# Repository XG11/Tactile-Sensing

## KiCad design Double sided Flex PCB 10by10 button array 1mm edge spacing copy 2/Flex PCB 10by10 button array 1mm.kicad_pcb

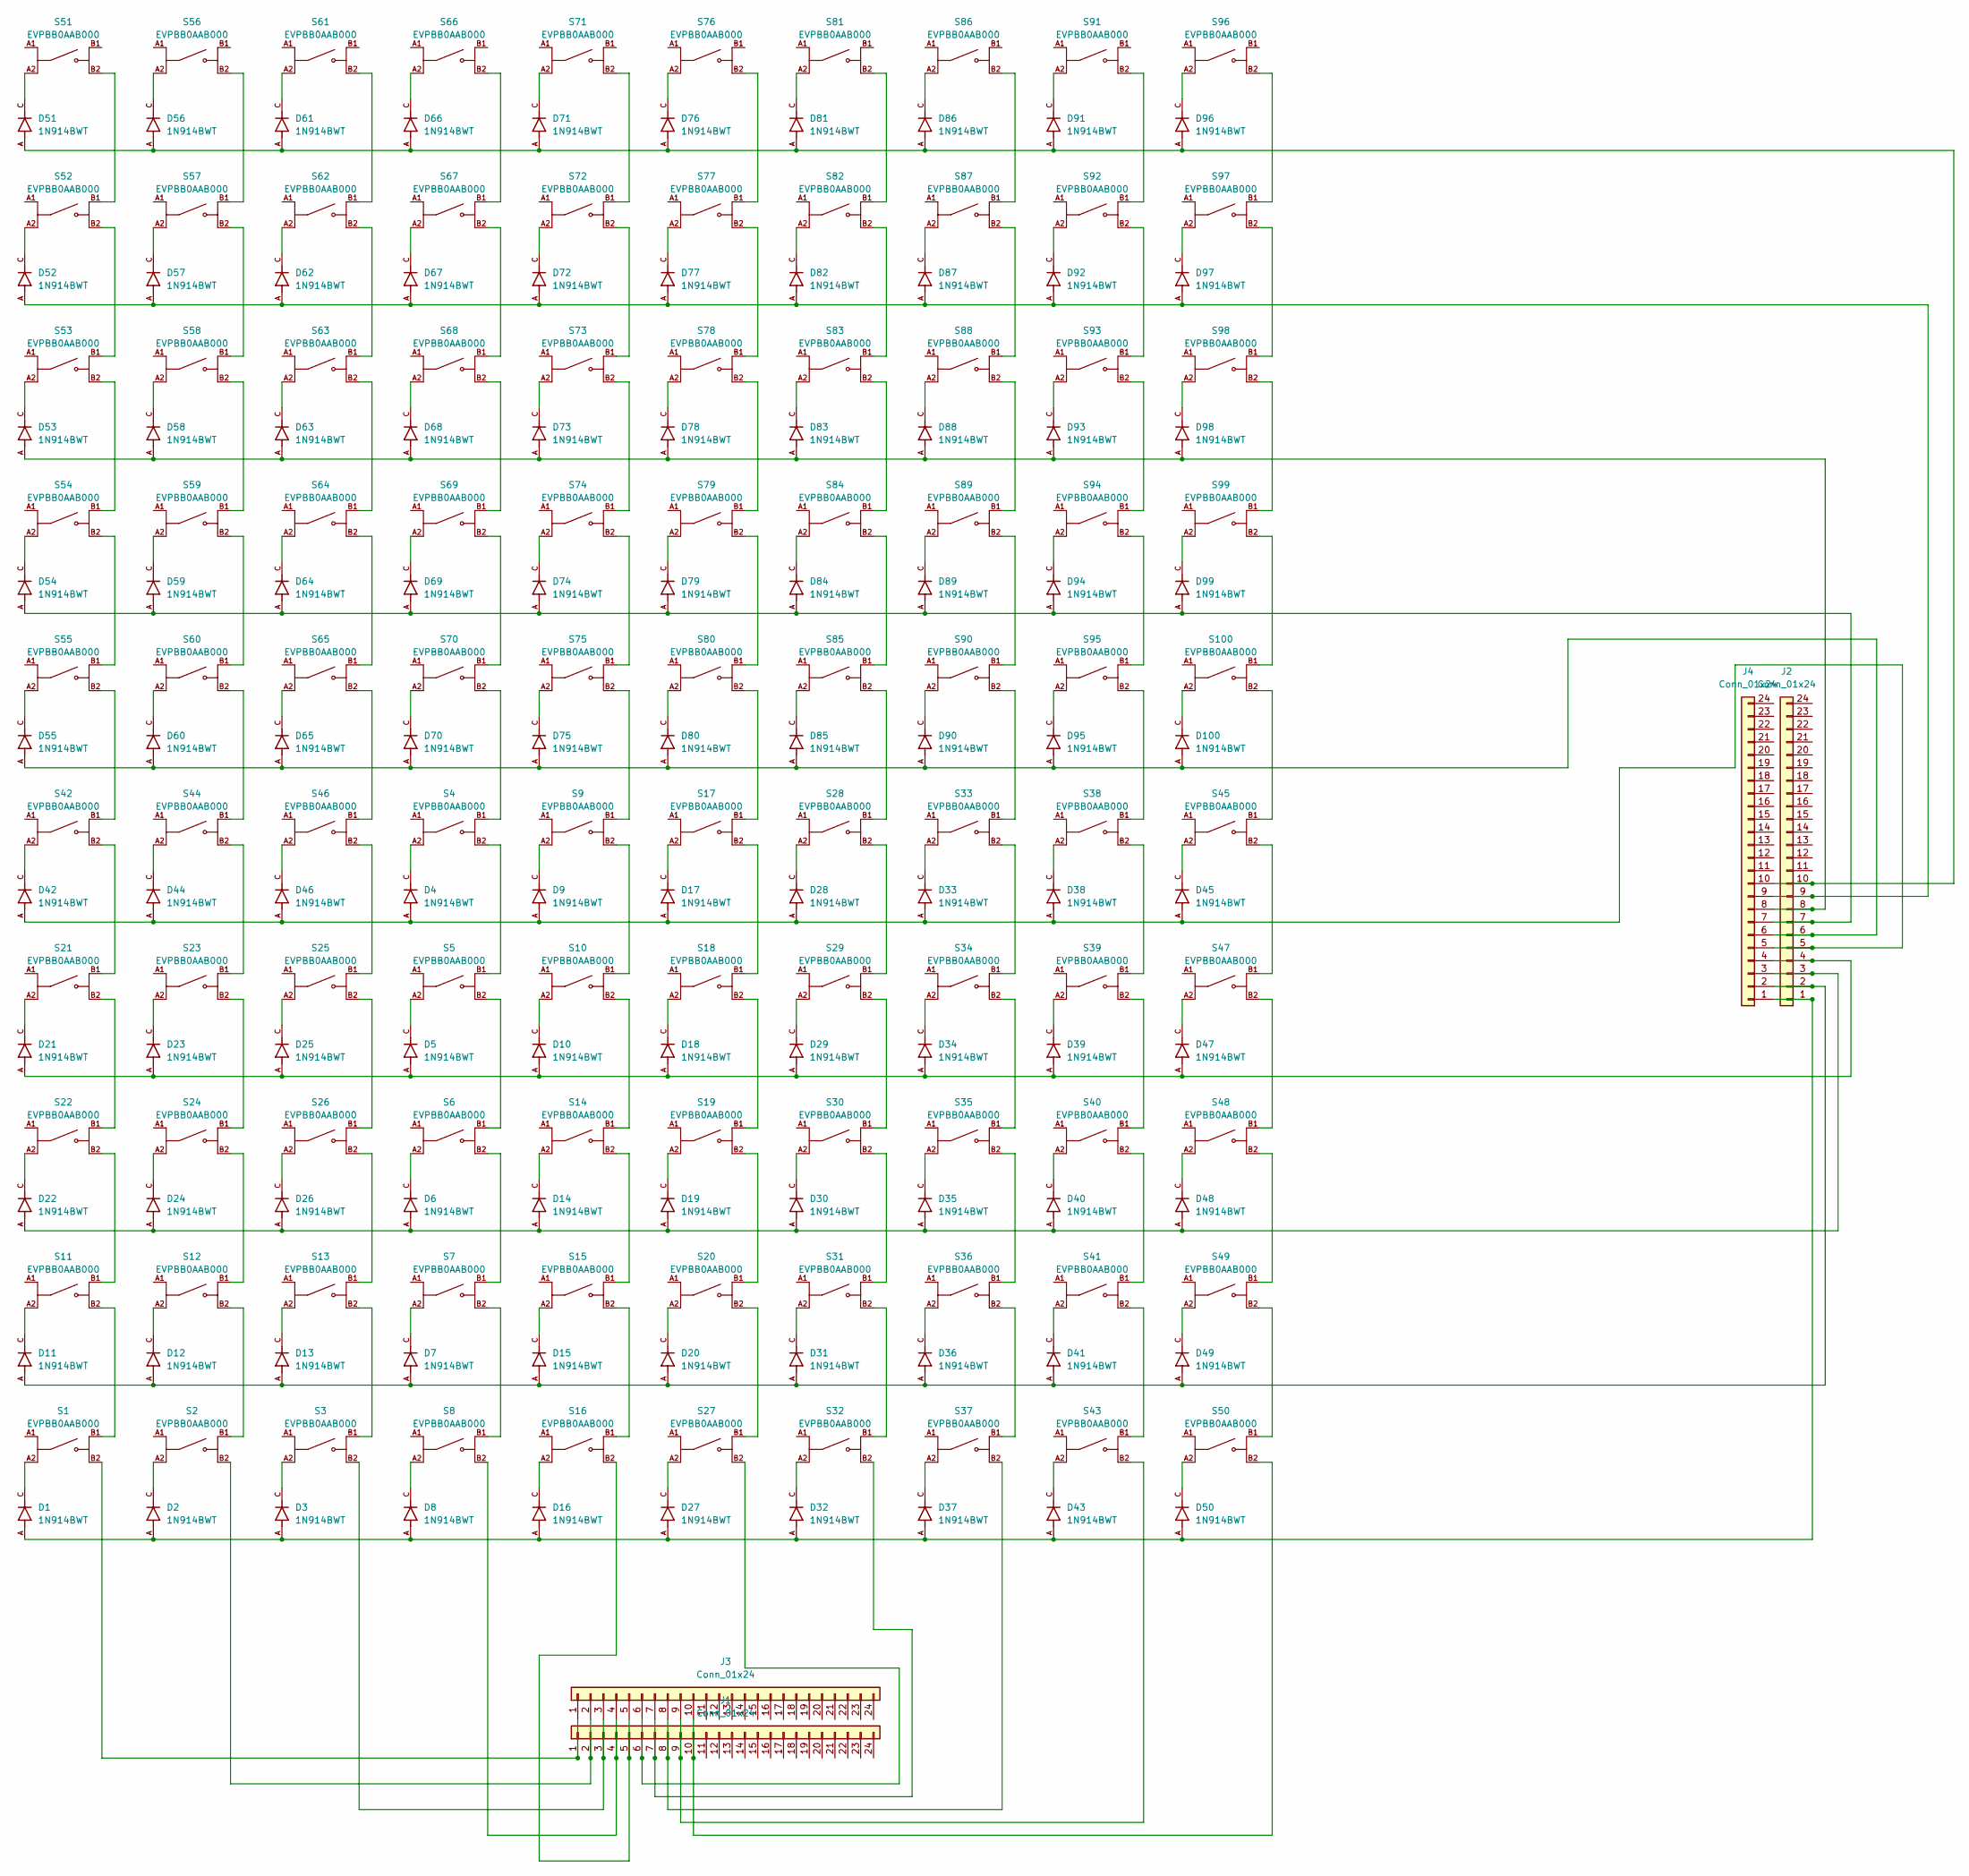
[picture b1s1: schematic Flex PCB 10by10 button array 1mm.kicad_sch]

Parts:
D1, D2, D3, D4, D5, D6, D7, D8, D9, D10, D11, D12, D13, D14, D15, D16, D17, D18, D19, D20, D21, D22, D23, D24, D25, D26, D27, D28, D29, D30, D31, D32, D33, D34, D35, D36, D37, D38, D39, D40, D41, D42, D43, D44, D45, D46, D47, D48, D49, D50, D51, D52, D53, D54, D55, D56, D57, D58, D59, D60, D61, D62, D63, D64, D65, D66, D67, D68, D69, D70, D71, D72, D73, D74, D75, D76, D77, D78, D79, D80, D81, D82, D83, D84, D85, D86, D87, D88, D89, D90, D91, D92, D93, D94, D95, D96, D97, D98, D99, D100: 1N914BWT; SODFL1608X70N; PARTREV A2
J1, J2, J3, J4: Conn_01x24; 24pos edge connector
S1, S2, S3, S4, S5, S6, S7, S8, S9, S10, S11, S12, S13, S14, S15, S16, S17, S18, S19, S20, S21, S22, S23, S24, S25, S26, S27, S28, S29, S30, S31, S32, S33, S34, S35, S36, S37, S38, S39, S40, S41, S42, S43, S44, S45, S46, S47, S48, S49, S50, S51, S52, S53, S54, S55, S56, S57, S58, S59, S60, S61, S62, S63, S64, S65, S66, S67, S68, S69, S70, S71, S72, S73, S74, S75, S76, S77, S78, S79, S80, S81, S82, S83, S84, S85, S86, S87, S88, S89, S90, S91, S92, S93, S94, S95, S96, S97, S98, S99, S100: EVPBB0AAB000; SW_EVPBB0AAB000; DIGI-KEY_PART_NUMBER P19888CT-ND

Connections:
unnamed: D1.C, S1.A2
unnamed: D2.C, S2.A2
unnamed: D3.C, S3.A2
unnamed: D4.C, S4.A2
unnamed: D5.C, S5.A2
unnamed: D6.C, S6.A2
unnamed: D7.C, S7.A2
unnamed: D8.C, S8.A2
unnamed: D9.C, S9.A2
unnamed: D10.C, S10.A2
unnamed: D11.C, S11.A2
unnamed: D12.C, S12.A2
unnamed: D13.C, S13.A2
unnamed: D14.C, S14.A2
unnamed: D15.C, S15.A2
unnamed: D16.C, S16.A2
unnamed: D17.C, S17.A2
unnamed: D18.C, S18.A2
unnamed: D19.C, S19.A2
unnamed: D20.C, S20.A2
unnamed: D21.C, S21.A2
unnamed: D22.C, S22.A2
unnamed: D23.C, S23.A2
unnamed: D24.C, S24.A2
unnamed: D25.C, S25.A2
unnamed: D26.C, S26.A2
unnamed: D27.C, S27.A2
unnamed: D28.C, S28.A2
unnamed: D29.C, S29.A2
unnamed: D30.C, S30.A2
unnamed: D31.C, S31.A2
unnamed: D32.C, S32.A2
unnamed: D33.C, S33.A2
unnamed: D34.C, S34.A2
unnamed: D35.C, S35.A2
unnamed: D36.C, S36.A2
unnamed: D37.C, S37.A2
unnamed: D38.C, S38.A2
unnamed: D39.C, S39.A2
unnamed: D40.C, S40.A2
unnamed: D41.C, S41.A2
unnamed: D42.C, S42.A2
unnamed: D43.C, S43.A2
unnamed: D44.C, S44.A2
unnamed: D45.C, S45.A2
unnamed: D46.C, S46.A2
unnamed: D47.C, S47.A2
unnamed: D48.C, S48.A2
unnamed: D49.C, S49.A2
unnamed: D50.C, S50.A2
unnamed: D51.C, S51.A2
unnamed: D52.C, S52.A2
unnamed: D53.C, S53.A2
unnamed: D54.C, S54.A2
unnamed: D55.C, S55.A2
unnamed: D56.C, S56.A2
unnamed: D57.C, S57.A2
unnamed: D58.C, S58.A2
unnamed: D59.C, S59.A2
unnamed: D60.C, S60.A2
unnamed: D61.C, S61.A2
unnamed: D62.C, S62.A2
unnamed: D63.C, S63.A2
unnamed: D64.C, S64.A2
unnamed: D65.C, S65.A2
unnamed: D66.C, S66.A2
unnamed: D67.C, S67.A2
unnamed: D68.C, S68.A2
unnamed: D69.C, S69.A2
unnamed: D70.C, S70.A2
unnamed: D71.C, S71.A2
unnamed: D72.C, S72.A2
unnamed: D73.C, S73.A2
unnamed: D74.C, S74.A2
unnamed: D75.C, S75.A2
unnamed: D76.C, S76.A2
unnamed: D77.C, S77.A2
unnamed: D78.C, S78.A2
unnamed: D79.C, S79.A2
unnamed: D80.C, S80.A2
unnamed: D81.C, S81.A2
unnamed: D82.C, S82.A2
unnamed: D83.C, S83.A2
unnamed: D84.C, S84.A2
unnamed: D85.C, S85.A2
unnamed: D86.C, S86.A2
unnamed: D87.C, S87.A2
unnamed: D88.C, S88.A2
unnamed: D89.C, S89.A2
unnamed: D90.C, S90.A2
unnamed: D91.C, S91.A2
unnamed: D92.C, S92.A2
unnamed: D93.C, S93.A2
unnamed: D94.C, S94.A2
unnamed: D95.C, S95.A2
unnamed: D96.C, S96.A2
unnamed: D97.C, S97.A2
unnamed: D98.C, S98.A2
unnamed: D99.C, S99.A2
unnamed: D100.C, S100.A2
unnamed: J1.1, J3.1, S1.B2
unnamed: J1.2, J3.2, S2.B2
unnamed: J1.3, J3.3, S3.B2
unnamed: J1.4, J3.4, S8.B2
unnamed: J1.5, J3.5, S16.B2
unnamed: J1.6, J3.6, S27.B2
unnamed: J1.7, J3.7, S32.B2
unnamed: J1.8, J3.8, S37.B2
unnamed: J1.9, J3.9, S43.B2
unnamed: J1.10, J3.10, S50.B2
unnamed: D1.A, D2.A, D3.A, D8.A, D16.A, D27.A, D32.A, D37.A, D43.A, D50.A, J2.1, J4.1
unnamed: D7.A, D11.A, D12.A, D13.A, D15.A, D20.A, D31.A, D36.A, D41.A, D49.A, J2.2, J4.2
unnamed: D6.A, D14.A, D19.A, D22.A, D24.A, D26.A, D30.A, D35.A, D40.A, D48.A, J2.3, J4.3
unnamed: D5.A, D10.A, D18.A, D21.A, D23.A, D25.A, D29.A, D34.A, D39.A, D47.A, J2.4, J4.4
unnamed: D4.A, D9.A, D17.A, D28.A, D33.A, D38.A, D42.A, D44.A, D45.A, D46.A, J2.5, J4.5
unnamed: D55.A, D60.A, D65.A, D70.A, D75.A, D80.A, D85.A, D90.A, D95.A, D100.A, J2.6, J4.6
unnamed: D54.A, D59.A, D64.A, D69.A, D74.A, D79.A, D84.A, D89.A, D94.A, D99.A, J2.7, J4.7
unnamed: D53.A, D58.A, D63.A, D68.A, D73.A, D78.A, D83.A, D88.A, D93.A, D98.A, J2.8, J4.8
unnamed: D52.A, D57.A, D62.A, D67.A, D72.A, D77.A, D82.A, D87.A, D92.A, D97.A, J2.9, J4.9
unnamed: D51.A, D56.A, D61.A, D66.A, D71.A, D76.A, D81.A, D86.A, D91.A, D96.A, J2.10, J4.10
unnamed: S1.B1, S11.B2
unnamed: S4.B1, S70.B2
unnamed: S4.B2, S5.B1
unnamed: S5.B2, S6.B1
unnamed: S6.B2, S7.B1
unnamed: S7.B2, S8.B1
unnamed: S9.B2, S10.B1
unnamed: S10.B2, S14.B1
unnamed: S11.B1, S22.B2
unnamed: S12.B1, S24.B2
unnamed: S2.B1, S12.B2
unnamed: S13.B1, S26.B2
unnamed: S3.B1, S13.B2
unnamed: S14.B2, S15.B1
unnamed: S15.B2, S16.B1
unnamed: S17.B1, S80.B2
unnamed: S17.B2, S18.B1
unnamed: S18.B2, S19.B1
unnamed: S19.B2, S20.B1
unnamed: S20.B2, S27.B1
unnamed: S21.B1, S42.B2
unnamed: S21.B2, S22.B1
unnamed: S23.B1, S44.B2
unnamed: S23.B2, S24.B1
unnamed: S25.B1, S46.B2
unnamed: S25.B2, S26.B1
unnamed: S28.B1, S85.B2
unnamed: S28.B2, S29.B1
unnamed: S29.B2, S30.B1
unnamed: S30.B2, S31.B1
unnamed: S31.B2, S32.B1
unnamed: S33.B1, S90.B2
unnamed: S33.B2, S34.B1
unnamed: S34.B2, S35.B1
unnamed: S35.B2, S36.B1
unnamed: S36.B2, S37.B1
unnamed: S38.B1, S95.B2
unnamed: S38.B2, S39.B1
unnamed: S39.B2, S40.B1
unnamed: S40.B2, S41.B1
unnamed: S41.B2, S43.B1
unnamed: S42.B1, S55.B2
unnamed: S44.B1, S60.B2
unnamed: S45.B2, S47.B1
unnamed: S46.B1, S65.B2
unnamed: S47.B2, S48.B1
unnamed: S48.B2, S49.B1
unnamed: S49.B2, S50.B1
unnamed: S51.B2, S52.B1
unnamed: S52.B2, S53.B1
unnamed: S53.B2, S54.B1
unnamed: S54.B2, S55.B1
unnamed: S56.B2, S57.B1
unnamed: S57.B2, S58.B1
unnamed: S58.B2, S59.B1
unnamed: S59.B2, S60.B1
unnamed: S61.B2, S62.B1
unnamed: S62.B2, S63.B1
unnamed: S63.B2, S64.B1
unnamed: S64.B2, S65.B1
unnamed: S66.B2, S67.B1
unnamed: S67.B2, S68.B1
unnamed: S68.B2, S69.B1
unnamed: S69.B2, S70.B1
unnamed: S71.B2, S72.B1
unnamed: S72.B2, S73.B1
unnamed: S73.B2, S74.B1
unnamed: S74.B2, S75.B1
unnamed: S9.B1, S75.B2
unnamed: S76.B2, S77.B1
unnamed: S77.B2, S78.B1
unnamed: S78.B2, S79.B1
unnamed: S79.B2, S80.B1
unnamed: S81.B2, S82.B1
unnamed: S82.B2, S83.B1
unnamed: S83.B2, S84.B1
unnamed: S84.B2, S85.B1
unnamed: S86.B2, S87.B1
unnamed: S87.B2, S88.B1
unnamed: S88.B2, S89.B1
unnamed: S89.B2, S90.B1
unnamed: S91.B2, S92.B1
unnamed: S92.B2, S93.B1
unnamed: S93.B2, S94.B1
unnamed: S94.B2, S95.B1
unnamed: S96.B2, S97.B1
unnamed: S97.B2, S98.B1
unnamed: S98.B2, S99.B1
unnamed: S99.B2, S100.B1
unnamed: S45.B1, S100.B2

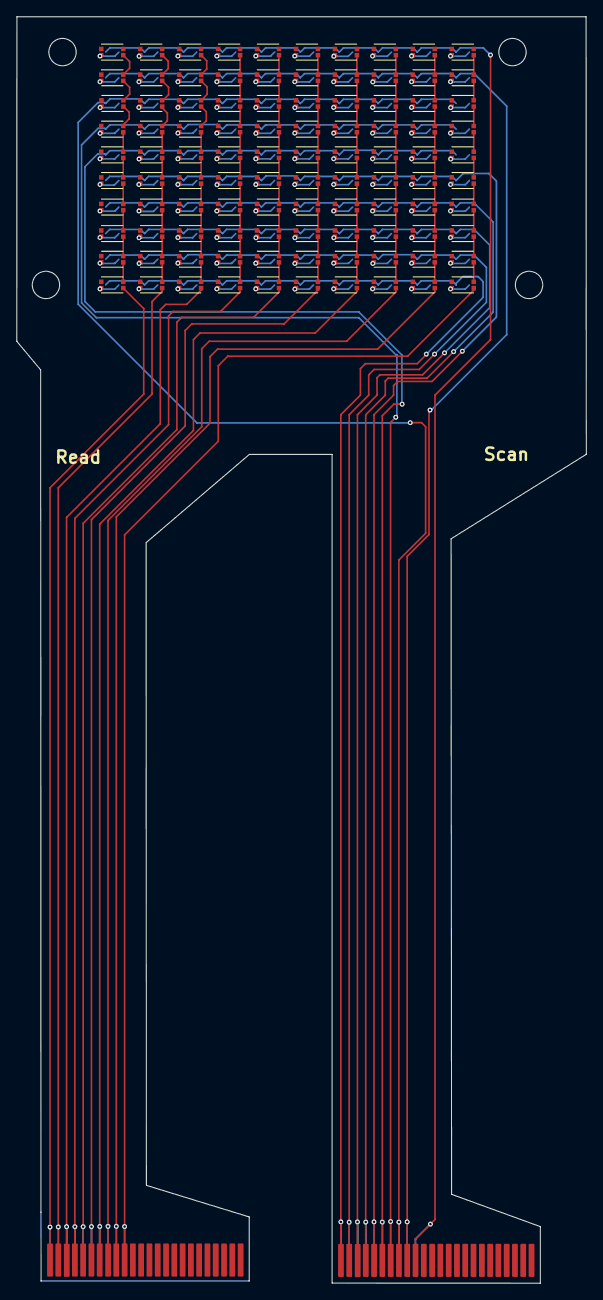
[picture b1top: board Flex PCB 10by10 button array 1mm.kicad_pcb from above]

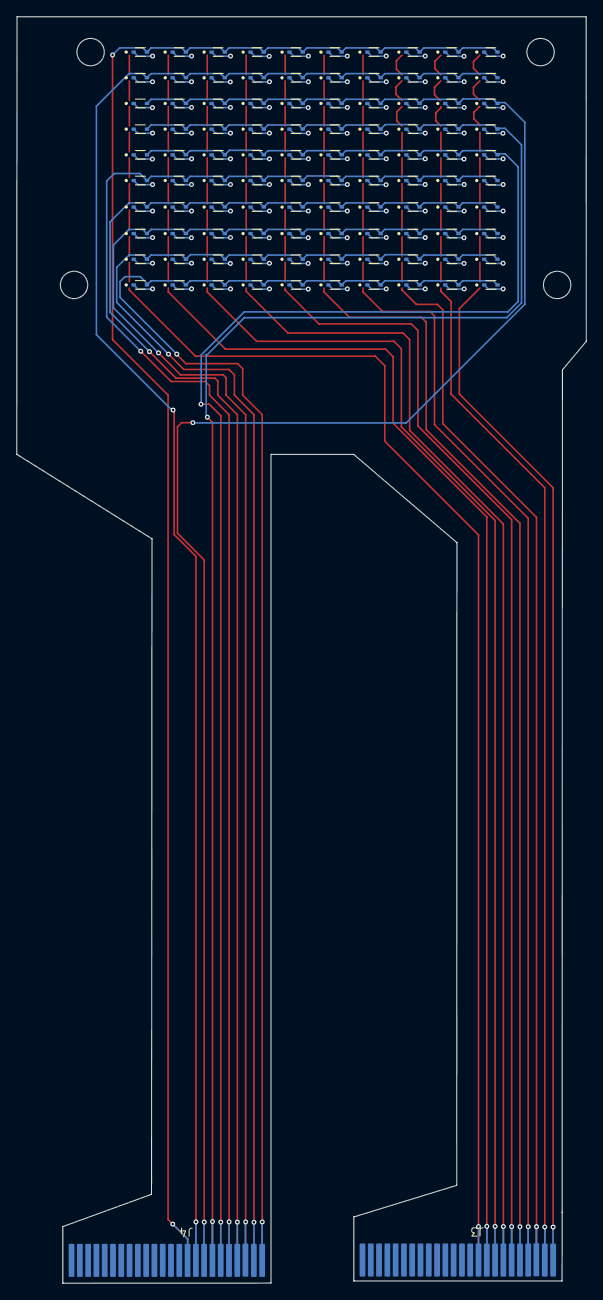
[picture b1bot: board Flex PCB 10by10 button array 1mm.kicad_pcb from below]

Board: 2 copper layers, 68.7 x 152.8 mm, 204 parts (102 on the bottom side), 210 nets.

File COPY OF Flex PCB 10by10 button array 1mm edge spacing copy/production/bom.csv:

Designator,Footprint,Quantity,Value,LCSC Part #
"D1, D10, D100, D11, D12, D13, D14, D15, D16, D17, D18, D19, D2, D20, D21, D22, D23, D24, D25, D26, D27, D28, D29, D3, D30, D31, D32, D33, D34, D35, D36, D37, D38, D39, D4, D40, D41, D42, D43, D44, D45, D46, D47, D48, D49, D5, D50, D51, D52, D53, D54, D55, D56, D57, D58, D59, D6, D60, D61, D62, D63, D64, D65, D66, D67, D68, D69, D7, D70, D71, D72, D73, D74, D75, D76, D77, D78, D79, D8, D80, D81, D82, D83, D84, D85, D86, D87, D88, D89, D9, D90, D91, D92, D93, D94, D95, D96, D97, D98, D99",SODFL1608X70N,100,1N914BWT,
"J1, J2",24pos edge connector,2,Conn_01x24,
"S1, S10, S100, S11, S12, S13, S14, S15, S16, S17, S18, S19, S2, S20, S21, S22, S23, S24, S25, S26, S27, S28, S29, S3, S30, S31, S32, S33, S34, S35, S36, S37, S38, S39, S4, S40, S41, S42, S43, S44, S45, S46, S47, S48, S49, S5, S50, S51, S52, S53, S54, S55, S56, S57, S58, S59, S6, S60, S61, S62, S63, S64, S65, S66, S67, S68, S69, S7, S70, S71, S72, S73, S74, S75, S76, S77, S78, S79, S8, S80, S81, S82, S83, S84, S85, S86, S87, S88, S89, S9, S90, S91, S92, S93, S94, S95, S96, S97, S98, S99",SW_EVPBB0AAB000,100,EVPBB0AAB000,

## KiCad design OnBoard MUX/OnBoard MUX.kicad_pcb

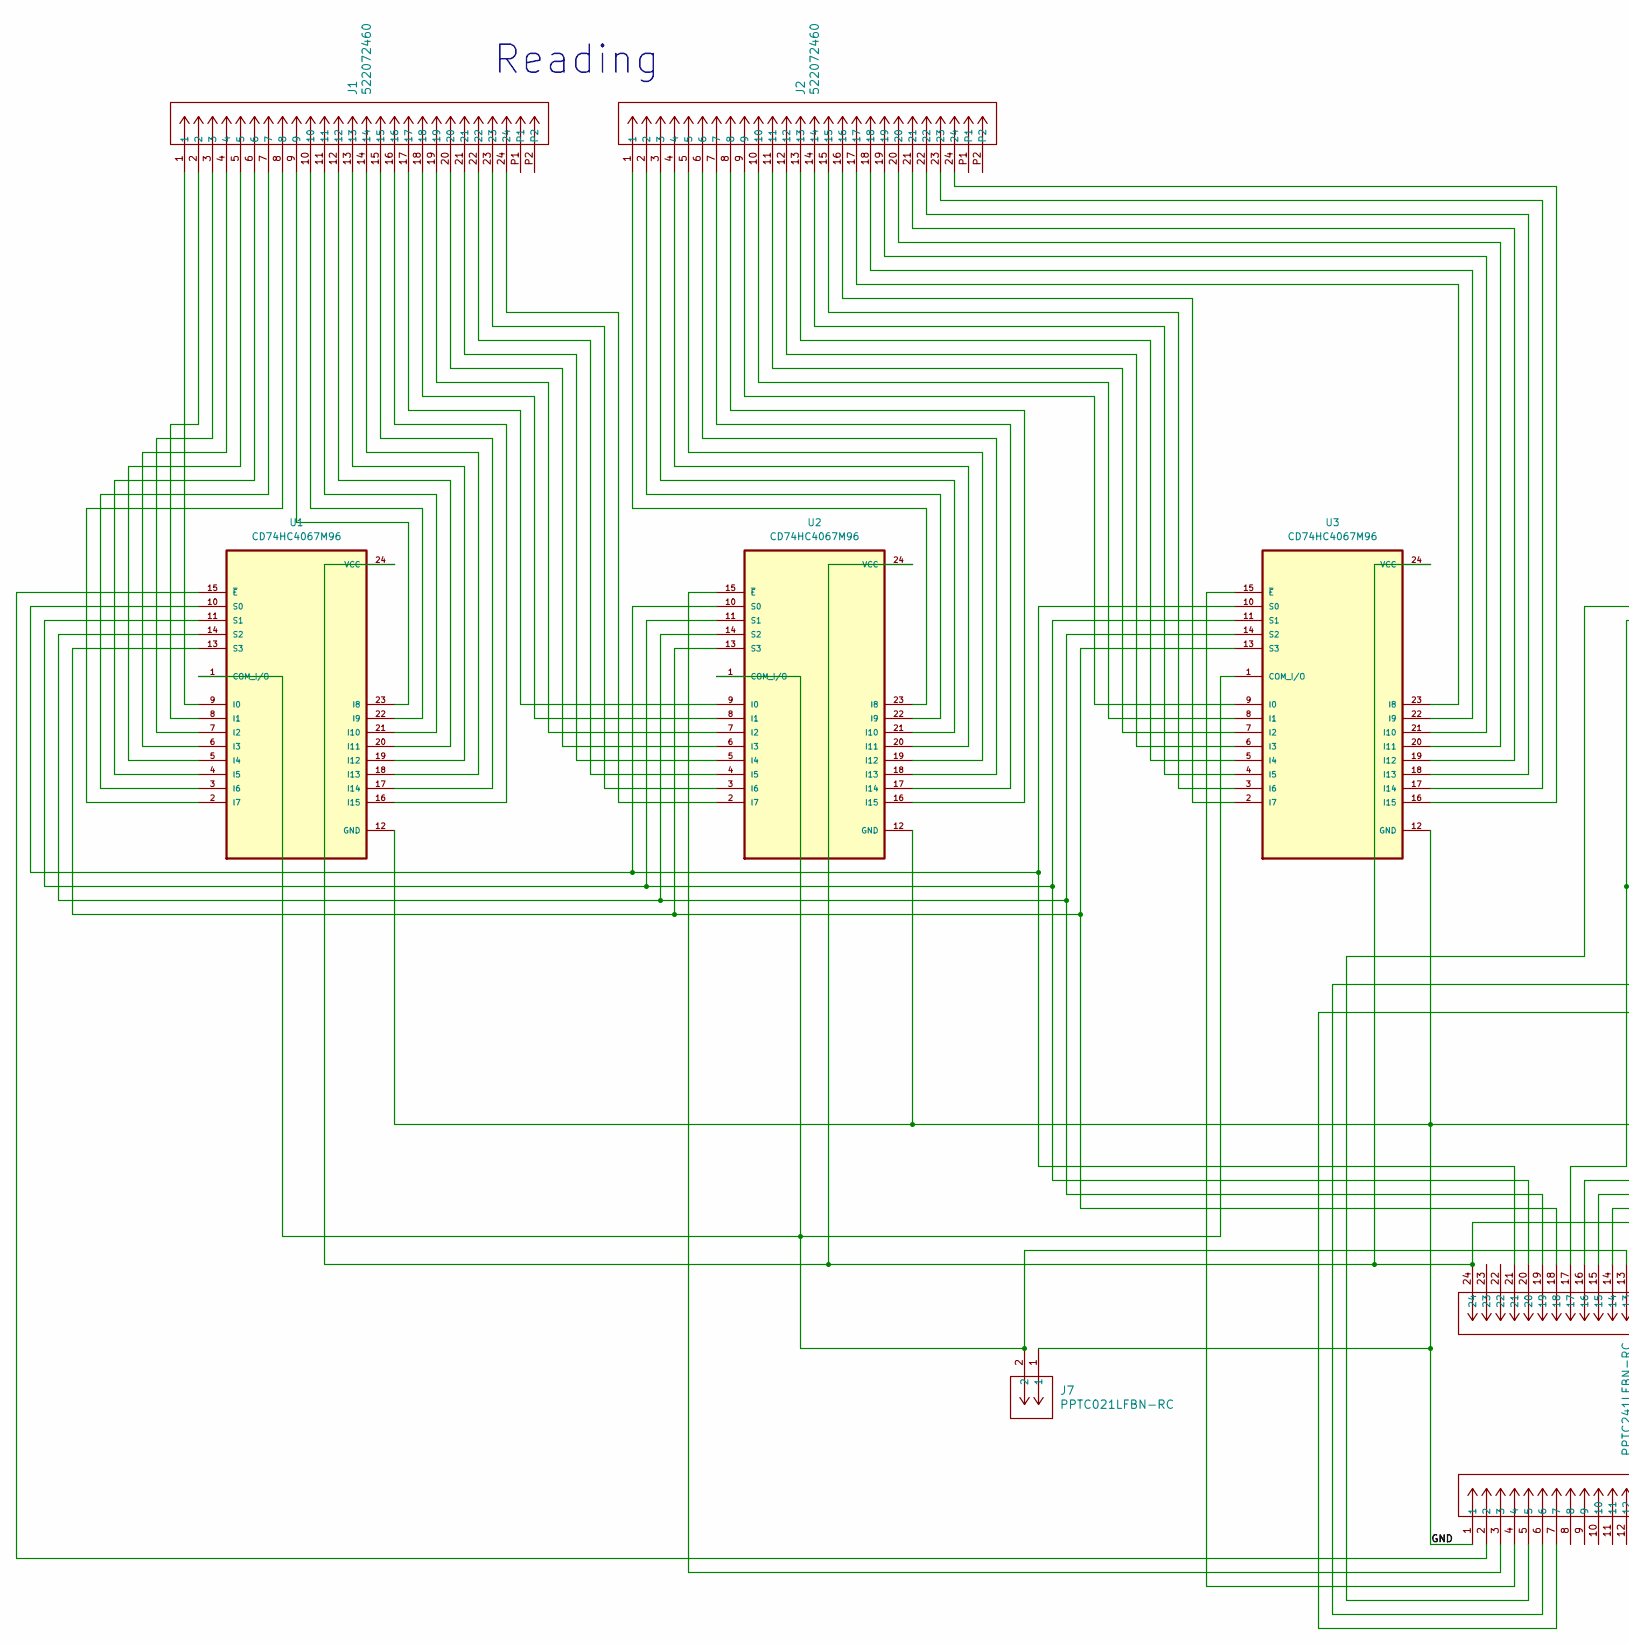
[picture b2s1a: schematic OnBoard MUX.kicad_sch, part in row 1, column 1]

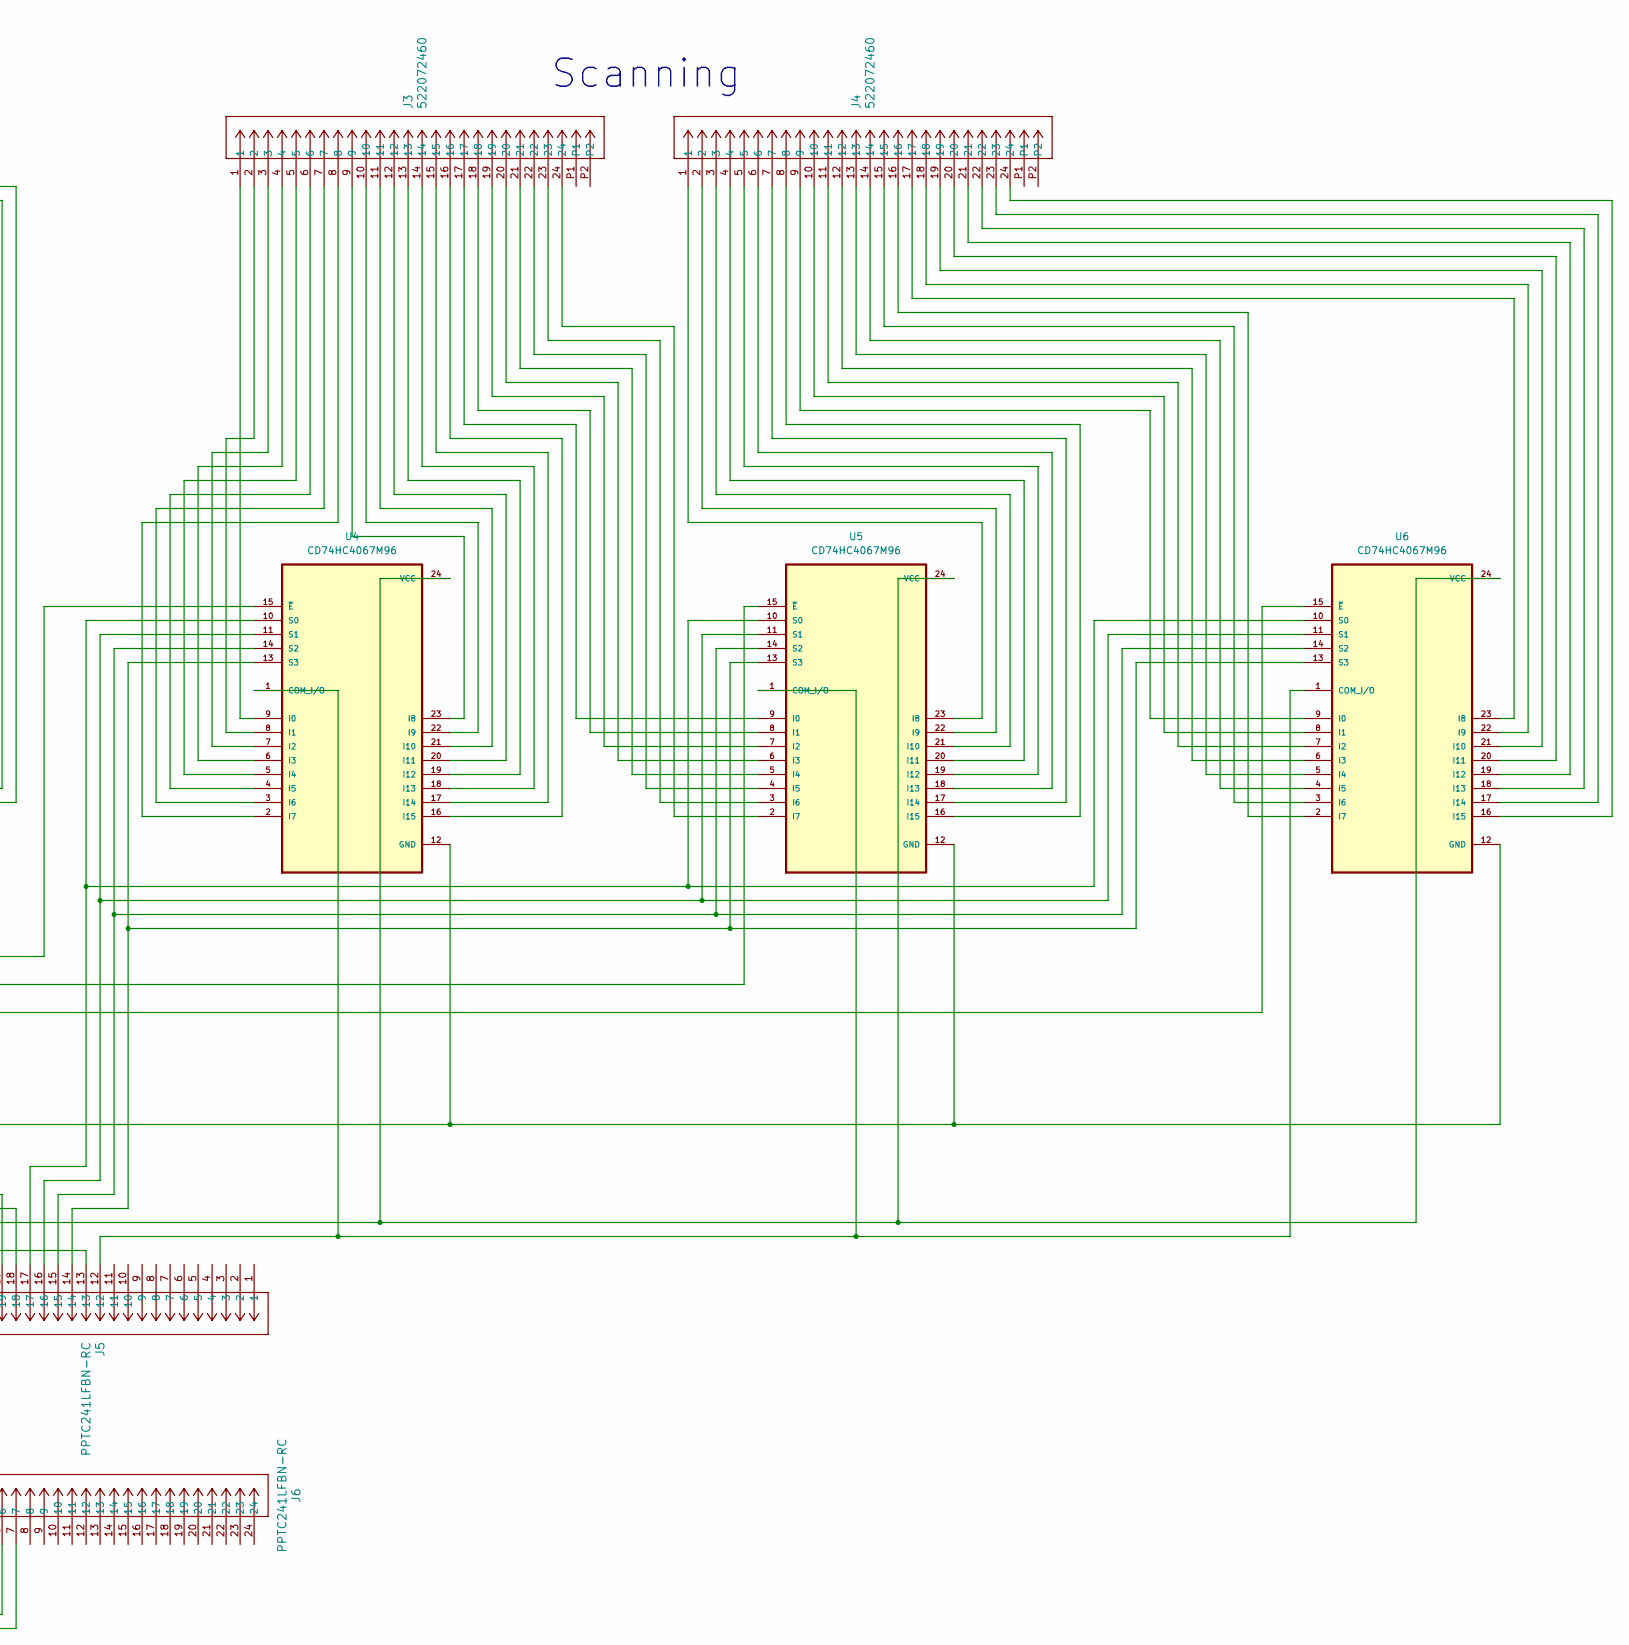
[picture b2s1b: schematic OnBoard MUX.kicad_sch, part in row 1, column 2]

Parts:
J1, J2, J3, J4: 522072460; CON_522072460_MOL
J5, J6: PPTC241LFBN-RC; CONN24_PPTC241LFBN-RC_SUL
J7: PPTC021LFBN-RC; CONN2_LFBN-RC_SUL
U1, U2, U3, U4, U5, U6: CD74HC4067M96; SOIC127P1030X265-24N

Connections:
/GND: J6.1, J7.1, U1.12 (GND), U2.12 (GND), U3.12 (GND), U4.12 (GND), U5.12 (GND), U6.12 (GND)
unnamed: J5.13, J7.2, U1.1 (COM_I/O), U2.1 (COM_I/O), U3.1 (COM_I/O)
unnamed: J1.1, U1.9 (I0)
unnamed: J1.2, U1.8 (I1)
unnamed: J1.3, U1.7 (I2)
unnamed: J1.4, U1.6 (I3)
unnamed: J1.5, U1.5 (I4)
unnamed: J1.6, U1.4 (I5)
unnamed: J1.7, U1.3 (I6)
unnamed: J1.8, U1.2 (I7)
unnamed: J1.9, U1.23 (I8)
unnamed: J1.10, U1.22 (I9)
unnamed: J1.11, U1.21 (I10)
unnamed: J1.12, U1.20 (I11)
unnamed: J1.13, U1.19 (I12)
unnamed: J1.14, U1.18 (I13)
unnamed: J1.15, U1.17 (I14)
unnamed: J1.16, U1.16 (I15)
unnamed: J5.21, U1.10 (S0), U2.10 (S0), U3.10 (S0)
unnamed: J5.20, U1.11 (S1), U2.11 (S1), U3.11 (S1)
unnamed: J5.19, U1.14 (S2), U2.14 (S2), U3.14 (S2)
unnamed: J5.18, U1.13 (S3), U2.13 (S3), U3.13 (S3)
unnamed: J5.24, U1.24 (VCC), U2.24 (VCC), U3.24 (VCC), U4.24 (VCC), U5.24 (VCC), U6.24 (VCC)
unnamed: J6.2, U1.15 (~E)
unnamed: J1.17, U2.9 (I0)
unnamed: J1.18, U2.8 (I1)
unnamed: J1.19, U2.7 (I2)
unnamed: J1.20, U2.6 (I3)
unnamed: J1.21, U2.5 (I4)
unnamed: J1.22, U2.4 (I5)
unnamed: J1.23, U2.3 (I6)
unnamed: J1.24, U2.2 (I7)
unnamed: J2.1, U2.23 (I8)
unnamed: J2.2, U2.22 (I9)
unnamed: J2.3, U2.21 (I10)
unnamed: J2.4, U2.20 (I11)
unnamed: J2.5, U2.19 (I12)
unnamed: J2.6, U2.18 (I13)
unnamed: J2.7, U2.17 (I14)
unnamed: J2.8, U2.16 (I15)
unnamed: J6.3, U2.15 (~E)
unnamed: J2.9, U3.9 (I0)
unnamed: J2.10, U3.8 (I1)
unnamed: J2.11, U3.7 (I2)
unnamed: J2.12, U3.6 (I3)
unnamed: J2.13, U3.5 (I4)
unnamed: J2.14, U3.4 (I5)
unnamed: J2.15, U3.3 (I6)
unnamed: J2.16, U3.2 (I7)
unnamed: J2.17, U3.23 (I8)
unnamed: J2.18, U3.22 (I9)
unnamed: J2.19, U3.21 (I10)
unnamed: J2.20, U3.20 (I11)
unnamed: J2.21, U3.19 (I12)
unnamed: J2.22, U3.18 (I13)
unnamed: J2.23, U3.17 (I14)
unnamed: J2.24, U3.16 (I15)
unnamed: J6.4, U3.15 (~E)
unnamed: J5.12, U4.1 (COM_I/O), U5.1 (COM_I/O), U6.1 (COM_I/O)
unnamed: J3.1, U4.9 (I0)
unnamed: J3.2, U4.8 (I1)
unnamed: J3.3, U4.7 (I2)
unnamed: J3.4, U4.6 (I3)
unnamed: J3.5, U4.5 (I4)
unnamed: J3.6, U4.4 (I5)
unnamed: J3.7, U4.3 (I6)
unnamed: J3.8, U4.2 (I7)
unnamed: J3.9, U4.23 (I8)
unnamed: J3.10, U4.22 (I9)
unnamed: J3.11, U4.21 (I10)
unnamed: J3.12, U4.20 (I11)
unnamed: J3.13, U4.19 (I12)
unnamed: J3.14, U4.18 (I13)
unnamed: J3.15, U4.17 (I14)
unnamed: J3.16, U4.16 (I15)
unnamed: J5.17, U4.10 (S0), U5.10 (S0), U6.10 (S0)
unnamed: J5.16, U4.11 (S1), U5.11 (S1), U6.11 (S1)
unnamed: J5.15, U4.14 (S2), U5.14 (S2), U6.14 (S2)
unnamed: J5.14, U4.13 (S3), U5.13 (S3), U6.13 (S3)
unnamed: J6.5, U4.15 (~E)
unnamed: J3.17, U5.9 (I0)
unnamed: J3.18, U5.8 (I1)
unnamed: J3.19, U5.7 (I2)
unnamed: J3.20, U5.6 (I3)
unnamed: J3.21, U5.5 (I4)
unnamed: J3.22, U5.4 (I5)
unnamed: J3.23, U5.3 (I6)
unnamed: J3.24, U5.2 (I7)
unnamed: J4.1, U5.23 (I8)
unnamed: J4.2, U5.22 (I9)
unnamed: J4.3, U5.21 (I10)
unnamed: J4.4, U5.20 (I11)
unnamed: J4.5, U5.19 (I12)
unnamed: J4.6, U5.18 (I13)
unnamed: J4.7, U5.17 (I14)
unnamed: J4.8, U5.16 (I15)
unnamed: J6.6, U5.15 (~E)
unnamed: J4.9, U6.9 (I0)
unnamed: J4.10, U6.8 (I1)
unnamed: J4.11, U6.7 (I2)
unnamed: J4.12, U6.6 (I3)
unnamed: J4.13, U6.5 (I4)
unnamed: J4.14, U6.4 (I5)
unnamed: J4.15, U6.3 (I6)
unnamed: J4.16, U6.2 (I7)
unnamed: J4.17, U6.23 (I8)
unnamed: J4.18, U6.22 (I9)
unnamed: J4.19, U6.21 (I10)
unnamed: J4.20, U6.20 (I11)
unnamed: J4.21, U6.19 (I12)
unnamed: J4.22, U6.18 (I13)
unnamed: J4.23, U6.17 (I14)
unnamed: J4.24, U6.16 (I15)
unnamed: J6.7, U6.15 (~E)

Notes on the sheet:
Reading
Scanning

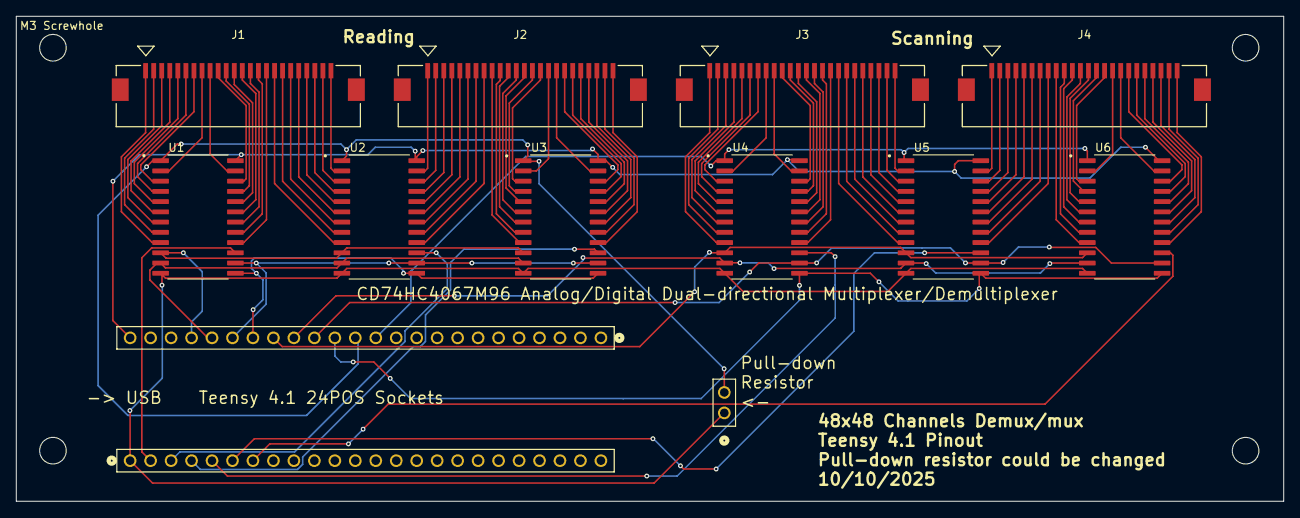
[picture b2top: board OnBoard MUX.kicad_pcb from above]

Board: 2 copper layers, 157.3 x 60.2 mm, 13 parts (0 on the bottom side), 114 nets.

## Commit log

2025-10-08 0.1mm edge spacing
2025-10-08 1mm edge spacing
